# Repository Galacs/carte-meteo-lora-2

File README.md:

# Carte meteo lora 2

## Pin definitions

```c
#define LORA_RST_PIN 24
#define LORA_DIO1_PIN 25
#define LORA_BUSY_PIN 27
#define LORA_DIO3_PIN 26
#define LORA_CS_PIN 3
#define LORA_SCK_PIN 2
#define LORA_MISO_PIN 4
#define LORA_MOSI 5

#define SCL_PIN 6
#define SDA_PIN 7

#define RGB_PIN 23
```

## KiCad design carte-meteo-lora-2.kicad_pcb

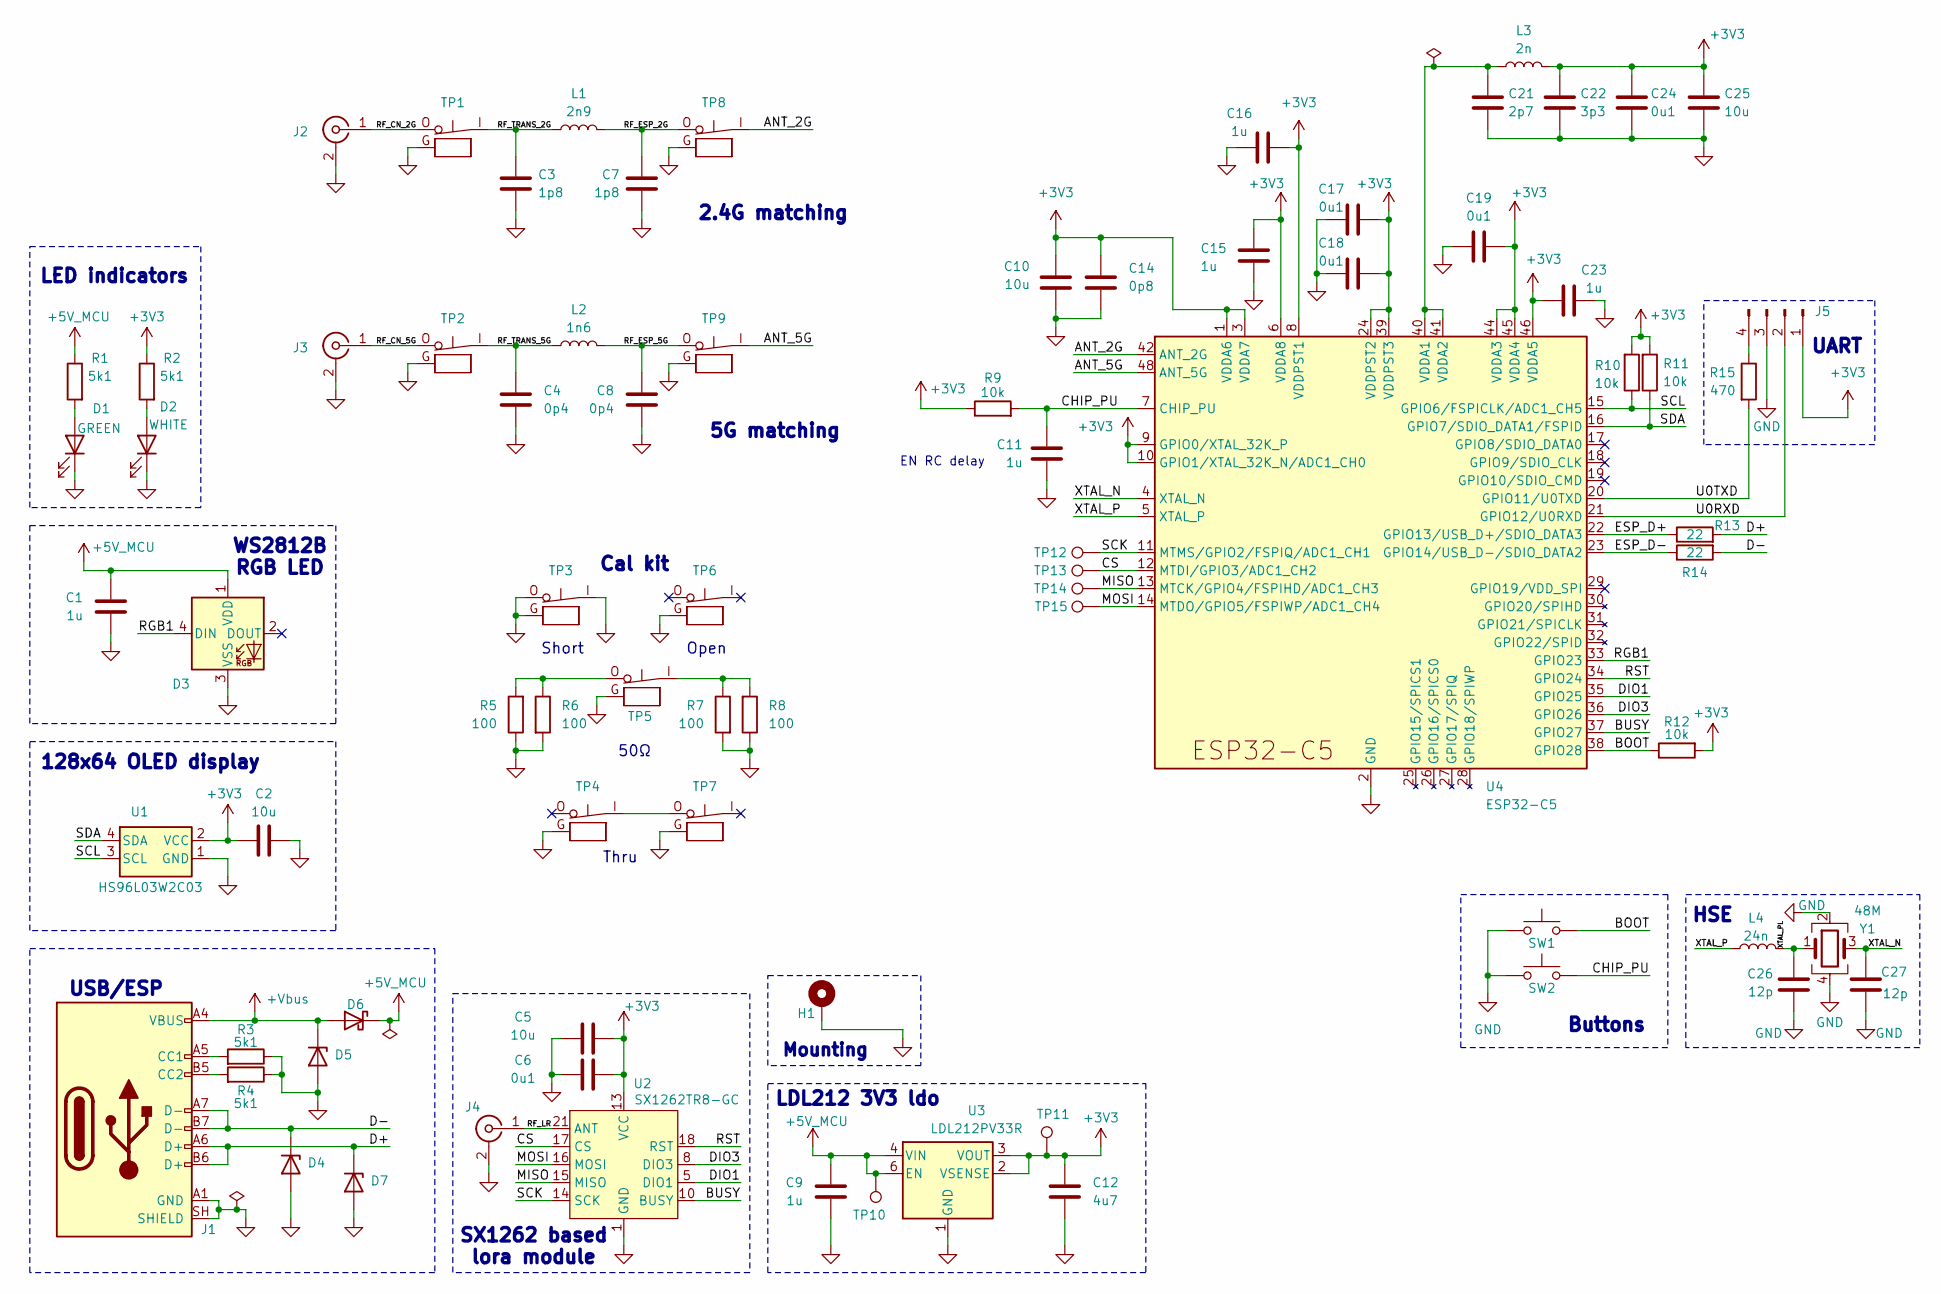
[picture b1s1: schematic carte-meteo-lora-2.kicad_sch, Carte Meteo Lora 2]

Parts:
C1, C9, C11, C15, C16, C23: 1u; C_0402_1005Metric; Manufacturer Part Number CL05A105KA5NQNC; JLCPCB Part # C52923
C2, C5, C10, C25: 10u; C_0402_1005Metric; Manufacturer Part Number CL05A106MQ5NUNC; JLCPCB Part # C15525
C3, C7: 1p8; C_0402_1005Metric; Manufacturer Part Number GJM1555C1H1R8WB01D; JLCPCB Part # C76903
C4, C8: 0p4; C_0402_1005Metric; Manufacturer Part Number GJM1555C1HR40BB01D; JLCPCB Part # C76910
C6, C17, C18, C19, C24: 0u1; C_0402_1005Metric; Manufacturer Part Number CL05B104KB54PNC; JLCPCB Part # C307331
C12: 4u7; C_0402_1005Metric; Manufacturer Part Number CL05A475MP5NRNC; JLCPCB Part # C23733
C14: 0p8; C_0402_1005Metric; Manufacturer Part Number CC0402BRNPO9BNR80; JLCPCB Part # C327032
C21: 2p7; C_0402_1005Metric; Manufacturer Part Number 0402CG2R7C500NT; JLCPCB Part # C1561
C22: 3p3; C_0402_1005Metric; Manufacturer Part Number 0402CG3R3C500NT; JLCPCB Part # C1565
C26, C27: 12p; C_0402_1005Metric; Manufacturer Part Number 0402CG120J500NT; JLCPCB Part # C1547
D1: GREEN; LED_0805_2012Metric; Manufacturer Part Number KT-0805G; JLCPCB Part # C2297
D2: WHITE; LED_0603_1608Metric; Manufacturer Part Number KT-0603W; JLCPCB Part # C2290
D3: WS2812B; LED_WS2812B_PLCC4_5.0x5.0mm_P3.2mm; Manufacturer Part Number WS2812B-V5/W; JLCPCB Part # C2874885
D4, D5, D7: H5VU10U; Diode_DFN1006; Manufacturer Part Number H5VU10U; JLCPCB Part # C22395519
D6: D_Schottky; D_SMA; Manufacturer Part Number SS54; JLCPCB Part # C22452
H1: MountingHole_Pad; MountingHole_2.2mm_M2_Pad_Via
J1: USB_C_Receptacle_USB2.0_14P; USB_C_Receptacle_HRO_TYPE-C-31-M-12; Manufacturer Part Number TYPE-C16PIN; JLCPCB Part # C393939
J2, J3, J4: Conn_Coaxial; SMA_BAT_Wireless_BWSMA-KWE-Z001; Manufacturer Part Number BWSMA-KWE-Z001; JLCPCB Part # C496551
J5: Conn_01x04_Pin; PinHeader_1x04_P2.54mm_Vertical
L1: 2n9; L_0402_1005Metric; Manufacturer Part Number MWI0402UC2N9JST-HF; JLCPCB Part # C48946217
L2: 1n6; L_0402_1005Metric; Manufacturer Part Number LQG15HS1N6S02D; JLCPCB Part # C162539
L3: 2n; L_0402_1005Metric; Manufacturer Part Number LQG15HS2N0S02D; JLCPCB Part # C18216
L4: 24n; L_0402_1005Metric; Manufacturer Part Number LQW15AN24NG00D; JLCPCB Part # C167472
R1, R2, R3, R4: 5k1; R_0402_1005Metric; Manufacturer Part Number 0402WGF5101TCE; JLCPCB Part # C25905
R5, R6, R7, R8: 100; R_0402_1005Metric; Manufacturer Part Number 0402WGF1000TCE; JLCPCB Part # C25076
R9, R10, R11, R12: 10k; R_0402_1005Metric; Manufacturer Part Number 0402WGF1002TCE; JLCPCB Part # C25744
R13, R14: 22; R_0402_1005Metric; Manufacturer Part Number 0402WGF220JTCE; JLCPCB Part # C25092
R15: 470; R_0402_1005Metric; Manufacturer Part Number 0402WGF4700TCE; JLCPCB Part # C25117
SW1, SW2: SW_Push; SW_SPST_TS-1088-xR020; Manufacturer Part Number TS-1088-AR02016; JLCPCB Part # C720477
TP1, TP2, TP3, TP4, TP5, TP6, TP7, TP8, TP9: RF_switch_connector; Murata_MM8930-2620; Manufacturer Part Number MM8930-2620RJ4; JLCPCB Part # C6227587
TP10, TP11: TestPoint; TestPoint_Pad_D2.0mm
TP12, TP13, TP14, TP15: TestPoint; TestPoint_Pad_D1.0mm
U1: HS96L03W2C03; Manufacturer Part Number HS96L03W2C03; JLCPCB Part # C5248080
U2: SX1262TR8-GC; Silicontra_SX1262ZTR8; Manufacturer Part Number SX1262TR8-GC; JLCPCB Part # C42381682
U3: LDL212PV33R; DFN-6-1EP_2x2mm_P0.5mm_ST; Manufacturer Part Number LDL212PV33R; JLCPCB Part # C2969892
U4: ESP32-C5; QFN-48-1EP_6x6mm_P0.4mm_EP4.6x4.6mm; Manufacturer Part Number ESP32-C5HF4
Y1: 48M; Crystal_SMD_2016-4Pin_2.0x1.6mm; Manufacturer Part Number R940000096; JLCPCB Part # C7206306

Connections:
+3V3: C2.2, C5.1, C6.2, C10.1, C12.1, C14.1, C15.2, C16.2, C17.2, C18.2, C19.1, C22.1, C23.1, C24.1, C25.1, J5.1, L3.2, R2.1, R9.1, R10.2, R11.2, R12.2, TP11.1 (1_1), U1.2 (VCC), U2.13 (VCC), U3.2 (VSENSE), U3.3 (VOUT), U4.1 (VDDA6), U4.3 (VDDA7), U4.6 (VDDA8), U4.8 (VDDPST1), U4.9 (GPIO0/XTAL_32K_P), U4.10 (GPIO1/XTAL_32K_N/ADC1_CH0), U4.24 (VDDPST2), U4.39 (VDDPST3), U4.44 (VDDA3), U4.45 (VDDA4), U4.46 (VDDA5)
+5V_MCU: C1.1, C9.1, D3.1 (VDD), D6.1 (K), R1.1, TP10.1 (1_1), U3.4 (VIN), U3.6 (EN)
+Vbus: D5.1 (K), D6.2 (A), J1.A4 (VBUS), J1.A9 (VBUS), J1.B4 (VBUS), J1.B9 (VBUS)
/ANT_2G: TP8.I, U4.42 (ANT_2G)
/ANT_5G: TP9.I, U4.48 (ANT_5G)
/BOOT: R12.1, SW1.2, U4.38 (GPIO28)
/BUSY: U2.10 (BUSY), U4.37 (GPIO27)
/CHIP_PU: C11.1, R9.2, SW2.2, U4.7 (CHIP_PU)
/CS: TP13.1 (1_1), U2.17 (CS), U4.12 (MTDI/GPIO3/ADC1_CH2)
/D+: D7.1 (K), J1.A6 (D+), J1.B6 (D+), R13.2
/D-: D4.1 (K), J1.A7 (D-), J1.B7 (D-), R14.2
/DIO1: U2.5 (DIO1), U4.35 (GPIO25)
/DIO3: U2.8 (DIO3), U4.36 (GPIO26)
/ESP_D+: R13.1, U4.22 (GPIO13/USB_D+/SDIO_DATA3)
/ESP_D-: R14.1, U4.23 (GPIO14/USB_D-/SDIO_DATA2)
/MISO: TP14.1 (1_1), U2.15 (MISO), U4.13 (MTCK/GPIO4/FSPIHD/ADC1_CH3)
/MOSI: TP15.1 (1_1), U2.16 (MOSI), U4.14 (MTDO/GPIO5/FSPIWP/ADC1_CH4)
/RF_CN_2G: J2.1 (In), TP1.O
/RF_CN_5G: J3.1 (In), TP2.O
/RF_ESP_2G: C7.1, L1.1, TP8.O
/RF_ESP_5G: C8.2, L2.1, TP9.O
/RF_LR: J4.1 (In), U2.21 (ANT)
/RF_TRANS_2G: C3.1, L1.2, TP1.I
/RF_TRANS_5G: C4.2, L2.2, TP2.I
/RGB1: D3.4 (DIN), U4.33 (GPIO23)
/RST: U2.18 (RST), U4.34 (GPIO24)
/SCK: TP12.1 (1_1), U2.14 (SCK), U4.11 (MTMS/GPIO2/FSPIQ/ADC1_CH1)
/SCL: R10.1, U1.3 (SCL), U4.15 (GPIO6/FSPICLK/ADC1_CH5)
/SDA: R11.1, U1.4 (SDA), U4.16 (GPIO7/SDIO_DATA1/FSPID)
/U0RXD: J5.2, U4.21 (GPIO12/U0RXD)
/U0TXD: R15.2, U4.20 (GPIO11/U0TXD)
/XTAL_N: C27.1, U4.4 (XTAL_N), Y1.3
/XTAL_P: L4.1, U4.5 (XTAL_P)
/XTAL_PL: C26.2, L4.2, Y1.1
GND: C1.2, C2.1, C3.2, C4.1, C5.2, C6.1, C7.2, C8.1, C9.2, C10.2, C11.2, C12.2, C14.2, C15.1, C16.1, C17.1, C18.1, C19.2, C21.2, C22.2, C23.2, C24.2, C25.2, C26.1, C27.2, D1.1 (K), D2.1 (K), D3.3 (VSS), D4.2 (A), D5.2 (A), D7.2 (A), H1.1 (1_1), J1.A1 (GND), J1.A12 (GND), J1.B1 (GND), J1.B12 (GND), J1.SH (SHIELD), J2.2 (Ext), J3.2 (Ext), J4.2 (Ext), J5.3, R3.1, R4.1, R5.1, R6.2, R7.2, R8.1, SW1.1, SW2.1, TP1.G, TP2.G, TP3.G, TP3.I, TP3.O, TP4.G, TP5.G, TP6.G (G_G), TP7.G, TP8.G, TP9.G, U1.1 (GND), U2.1 (GND), U2.2 (GND), U2.3 (GND), U2.4 (GND), U2.11 (GND), U2.12 (GND), U2.19 (GND), U2.20 (GND), U2.22 (GND), U3.1 (GND), U4.2 (GND), U4.43 (GND), U4.47 (GND), U4.49 (GND), Y1.2, Y1.4
unnamed: D1.2 (A), R1.2
unnamed: D2.2 (A), R2.2
unnamed: J1.A5 (CC1), R3.2
unnamed: J1.B5 (CC2), R4.2
unnamed: J5.4, R15.1
unnamed: R5.2, R6.1, TP5.O
unnamed: R7.1, R8.2, TP5.I
unnamed: TP4.I, TP7.O
unnamed: C21.1, L3.1, U4.40 (VDDA1), U4.41 (VDDA2)

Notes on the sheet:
2.4G matching
EN RC delay
Thru
Cal kit
LED indicators
WS2812B RGB LED
HSE
SX1262 based lora module
Short
50Ω
USB/ESP
5G matching
LDL212 3V3 ldo
Buttons
UART
Mounting
128x64 OLED display
Open

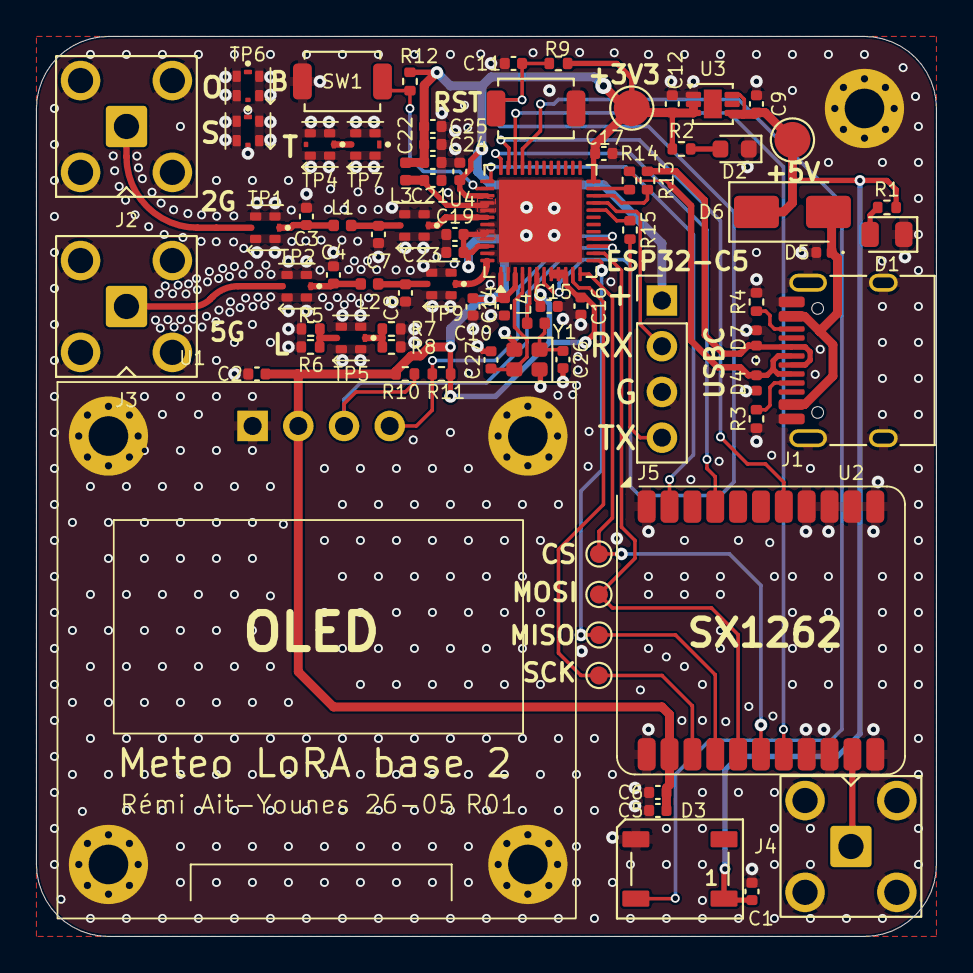
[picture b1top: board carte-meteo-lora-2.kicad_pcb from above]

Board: 4 copper layers, 50.0 x 50.0 mm, 79 parts (0 on the bottom side), 44 nets.

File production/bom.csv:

Designator,Footprint,Quantity,Value,LCSC Part #
"C1, C11, C15, C16, C23, C9",0402,6,1u,C52923
"C10, C2, C25, C5",0402,4,10u,C15525
C12,0402,1,4u7,C23733
C14,0402,1,0p8,C327032
"C17, C18, C19, C24, C6",0402,5,0u1,C307331
C21,0402,1,2p7,C1561
C22,0402,1,3p3,C1565
"C26, C27",0402,2,12p,C1547
"C3, C7",0402,2,1p8,C76903
"C4, C8",0402,2,0p4,C76910
D1,0805,1,GREEN,C2297
D2,0603,1,WHITE,C2290
D3,LED_WS2812B_PLCC4_5.0x5.0mm_P3.2mm,1,WS2812B,C2874885
"D4, D5, D7",Diode_DFN1006,3,H5VU10U,C22395519
D6,D_SMA,1,D_Schottky,C22452
J1,USB_C_Receptacle_HRO_TYPE-C-31-M-12,1,USB_C_Receptacle_USB2.0_14P,C393939
"J2, J3, J4",SMA_BAT_Wireless_BWSMA-KWE-Z001,3,Conn_Coaxial,C496551
L1,0402,1,2n9,C48946217
L2,0402,1,1n6,C162539
L3,0402,1,2n,C18216
L4,0402,1,24n,C167472
"R1, R2, R3, R4",0402,4,5k1,C25905
"R10, R11, R12, R9",0402,4,10k,C25744
"R13, R14",0402,2,22,C25092
R15,0402,1,470,C25117
"R5, R6, R7, R8",0402,4,100,C25076
"SW1, SW2",SW_SPST_TS-1088-xR020,2,SW_Push,C720477
"TP1, TP2, TP3, TP4, TP5, TP6, TP7, TP8, TP9",Murata_MM8930-2620,9,RF_switch_connector,C6227587
U1,HS96L03W2C03,1,HS96L03W2C03,C5248080
U2,Silicontra_SX1262ZTR8,1,SX1262TR8-GC,C42381682
U3,DFN-6-1EP_2x2mm_P0.5mm_ST,1,LDL212PV33R,C2969892
U4,QFN-48-1EP_6x6mm_P0.4mm_EP4.6x4.6mm,1,ESP32-C5,
Y1,Crystal_SMD_2016-4Pin_2.0x1.6mm,1,48M,C7206306

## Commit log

2026-05-25 schem: add boot/rst buttons
2026-05-25 schem: add LDL212 3V3 ldo
2026-05-25 schem: connect gpios to mcu
2026-05-26 schem: add cal kit
2026-05-26 schem: add no connects
2026-05-26 schem: add led pwr indicators
2026-05-26 schem: add test points
2026-05-26 schem: add net classes
2026-05-26 schem: assign footprints
2026-05-26 schem: add title
2026-05-26 schem: add ordering info to BOM
2026-05-26 schem: renumber
2026-05-26 pcb: import 4 layer jlc stackup
2026-05-26 pcb: import footprints from schem
2026-05-26 pcb: add missing 3d models
2026-05-27 pcb: initial sectioning
2026-05-27 pcb: add usb inital layout
2026-05-27 pcb: add initial rf layout
2026-05-27 pcb: add initial crystal layout
2026-05-27 pcb: initial section
2026-05-27 pcb: add edge cut
2026-05-27 pcb: add m2 mouting holes
2026-05-27 pcb: add inital layout
2026-05-27 pcb: add gnd vias
2026-05-27 pcb: add grid/place origin
2026-05-27 pcb: reorganize programmable gpios
2026-05-27 pcb: add rf routing
2026-05-27 pcb: add crystal routing
2026-05-27 pcb: add usb routing
2026-05-27 pcb: add uart routing
2026-05-27 pcb: add i2c routing
2026-05-27 pcb: add lora module routing
2026-05-27 pcb: add +3v3 pwr routing
2026-05-29 pcb: finish routing 3v3
2026-05-29 pcb: add +5v pwr routing
2026-05-29 pcb: route boot and rst
2026-05-29 pcb: clean up traces
2026-05-29 pcb: add stitching vias
2026-05-29 pcb: run and fix DRC
2026-05-29 pcb: remove unused internal pads
2026-05-29 pcb(silk): clean up reference designators
2026-05-29 pcb(silk): add user txt
2026-05-29 pcb: add title
2026-05-29 pcb: add lora missing 3d model
2026-05-29 generate production files
2026-05-30 pcb: add base station graphic
2026-05-30 pcb(silk): add indications
2026-05-30 regenerate production files
2026-06-08 docs: add pin definitions
